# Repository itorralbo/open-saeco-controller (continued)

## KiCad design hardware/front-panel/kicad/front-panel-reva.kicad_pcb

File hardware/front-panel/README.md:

# Frontal Rev A.0

Decisión del propietario, 2026-09-16: reproducir la PCB frontal para conservar
la disposición de botones y montar una pantalla nueva compatible con el hueco.
Se conserva como objetivo la geometría original. El 2026-09-18 se recuperaron por
fotogrametría contorno, taladros y centros de los siete pulsadores (184 × 54,3 mm);
están aceptadas como línea base del layout y aplicadas a la PCB de trabajo. Ver
[registro mecánico](mechanical.md).

Estado del layout (2026-09-18): **PCB colocada y ruteada, DRC limpio y paquete JLCPCB
candidato**, pendiente de revisión antes de pedir. Ver [layout](layout.md).

## Entregables de esta iteración

- [Esquema KiCad](kicad/front-panel-reva.kicad_sch), con símbolos embebidos.
- [Proyecto KiCad](kicad/front-panel-reva.kicad_pro) y
  [PCB](kicad/front-panel-reva.kicad_pcb) colocada y ruteada, con huella propia de
  los pulsadores en [OpenSaeco.pretty](kicad/OpenSaeco.pretty/).
- [Layout, mapa de teclas y registros del TCA9534](layout.md);
  vistas [superior](preview/pcb-top.png) e [inferior](preview/pcb-bottom.png).
- [Paquete JLCPCB candidato](fabrication/): Gerber y taladros, BOM y CPL.
- [Vista nativa de KiCad](validation/front-panel-reva.svg) y
  [validación y límites](../kicad-workflow.md).
- [Vista SVG del circuito](preview/front-panel.svg), generada como ayuda de revisión.
- [BOM candidata](bom-draft.csv) y [conexiones previstas](design-nets.json).
- [Contrato con la principal](../controller/front-panel-interface.md).
- [Registro mecánico fotogramétrico](mechanical.md), [datos](mechanical-source.json)
  y [plano 1:1 imprimible](validation/mechanical-1to1.svg).
- [Selección de componentes y montaje JLCPCB](../assembly/README.md): 42 de 42
  posiciones con MPN y código JLC; J1 (Würth WR-MM) sin stock en JLCPCB el
  2026-10-08, se compra aparte y se suelda a mano.

El circuito contiene alimentación externa de 3,3 V, un TCA9534PWR, siete canales
de pulsador filtrados (los siete de la PCB original), el LED de standby en el octavo
puerto y una salida a adaptador de display SPI. ERC y DRC nativos limpios. No está
pedido: faltan las comprobaciones de [layout.md](layout.md#pendiente-antes-de-pedir).

## Circuito propuesto

El ESP32 permanece en la controladora principal. Lee botones por I²C y escribe
la pantalla por SPI. El STM32 recibe solicitudes a través del protocolo del
proyecto y conserva la autoridad sobre las cargas.

U1 es un **TCA9534PWR, TSSOP-16**. A0/A1/A2 van a masa, dirección de siete bits
`0x20`. Sus ocho puertos arrancan como entradas; P0–P6 leen teclas y P7 se configura
como salida para el LED (ver [layout.md](layout.md#teclas-led-y-registros-del-tca9534)).
INT es una salida activa a nivel
bajo de drenador abierto. Ver pinout y registros en la
[hoja de datos TI SCPS197D](https://www.ti.com/lit/ds/symlink/tca9534.pdf),
§5, §8.5 y §8.6. El esquema y la BOM se refieren al TCA9534, no al TCA9534A.

Cada canal de tecla tiene 10 kΩ a 3,3 V, 100 nF a masa y un pulsador normalmente abierto
a masa a través de 1 kΩ. La resistencia serie limita la corriente si un error
configura el puerto como salida alta. Estimación nominal: 0,30 V pulsado,
0,30 mA por pulsador y constante de subida de 1 ms. El RC reduce ruido;
el antirrebote temporal sigue siendo necesario.

R1/R2 = 4,7 kΩ son las únicas pull-ups I²C previstas. R3 = 10 kΩ polariza INT.
C1 = 100 nF y C2 = 1 µF quedan junto a U1; C3 = 10 µF, junto al pin 1 de J1.
Las huellas 0603 tienen referencias de compra candidatas en la BOM; falta comprobar
capacitancia efectiva, temperatura, corriente y espacio. Se usan X7R para 100 nF
y X5R para 1 µF/10 µF según el catálogo de montaje consultado. Pulsadores: HRO
K2-1102SP-A4SC-04 (JLC C83916), 6 × 6 × 4,3 mm como el original medido.
LED STBY: KT-0603R rojo (C2286) con R7 = 470 Ω a 3,3 V, activo con P7 a 0.

J2 lleva alimentación, masa, MOSI, reloj, CS, DC, RESET y BL. CS y RESET
tienen pull-up; BL tiene pull-down para solicitar retroiluminación apagada al
arranque. **BL es una señal lógica**, prevista para un módulo con driver de LED.
No alimentar directamente una retroiluminación desde ese GPIO. J2 es un JST PH de
8 vías vertical (B8B-PH-K-S, JLC C157974) con el orden del cable PH del módulo
Waveshare 2" (VCC GND DIN CLK CS DC RST BL), útil para el banco. El adaptador
definitivo deberá respetar ese orden y añadir driver si lo necesita la pantalla.

J1 es el Würth WR-MM 690367181672 que el propietario identificó el 2026-10-01 en
el JP3 original, igual que J104 de la principal: 16 contactos a 1,27 mm al
tresbolillo. El cable original es plano, de 16 hilos y 1:1; su pestillo entra en
un taladro de 1,5 mm junto al pin 1, que lo retiene y fija el sentido. Va sobre la
zona del JP3 original, en su pestaña, cara de componentes. JLCPCB lo lista como C19103863 sin stock (2026-10-01).

## Pantalla reemplazable

> Decisión registrada (2026-09-18): se adopta un **TFT ST7789 2,0"** (240×320, SPI 4 hilos, 3,3 V) sobre frontal nuevo; se descarta reutilizar la PCB OEM. Ver [ADR-0001](../../docs/adr/0001-front-panel-display-st7789.md) y el [subsistema display + UI](../../docs/display-ui.md) (stack LVGL 9 + esp_lcd, SPI 10 MHz, presupuestos y árbol de pantallas). La tabla siguiente se conserva como registro de evaluación de hueco.

La compatibilidad se define por ventana visible, contorno total, altura,
orientación, lógica de 3,3 V, consumo y protocolo. La diagonal sola no basta.
La PCB de botones y el adaptador del display serán diseños independientes,
para cambiar de pantalla sin recolocar los pulsadores.

Referencias para comparar dimensiones, **sin selección ni compra todavía**:

| Módulo candidato | Controlador / resolución | Área visible (mm) | PCB del módulo (mm) |
|---|---|---|---|
| Waveshare 2 inch LCD Module | ST7789VW / 240 × 320 | 30,60 × 40,80 | 58,0 × 35,0 |
| Waveshare 2.4 inch LCD Module | ILI9341 / 240 × 320 | 36,72 × 48,96 | 70,50 × 43,30 |

Fuentes del fabricante consultadas el 2026-09-16:
[módulo 2 pulgadas](https://www.waveshare.com/product/displays/lcd-oled/2inch-lcd-module.htm)
y [módulo 2,4 pulgadas](https://www.waveshare.com/product/2.4inch-lcd-module.htm).
Para el segundo, el fabricante vincula el nivel lógico a la alimentación:
se evaluará alimentado a 3,3 V, no a 5 V.

Estos módulos sirven para evaluar el hueco y prototipar. El diseño final puede
necesitar un panel sin carrier comercial. J2 no incorpora MISO ni táctil:
un display que necesite lectura, touch o interfaz RGB/paralela requiere revisar
el adaptador y las señales disponibles, no solo cambiar el controlador software.

## Comportamiento de firmware previsto

1. Mantener BL bajo y CS alto durante la inicialización. Aplicar el reset y los
   tiempos del display finalmente seleccionado antes de habilitar la imagen.
2. Configurar U1 en este orden: Output (`0x01`) = `0xFF` (LED apagado), Polarity
   (`0x02`) = `0x00`, Configuration (`0x03`) = `0x7F`; leer Input (`0x00`) con los
   bits 0–6. P7 (bit 7 de Output) solo controla el LED, activo a 0.
3. Leer cada 5 ms como punto de partida y exigir 20 ms de estabilidad.
   INT permite adelantar una lectura; conservar el sondeo para detectar fallos.
   Son objetivos iniciales de firmware, aún no implementados ni ensayados.
4. Tras arranque/reconexión, esperar liberación de todos los botones antes de
   aceptar una pulsación. No convertir una tecla mantenida en START al reiniciar.
5. NACK, lectura caducada o fallo del bus invalidan el teclado: no equivalen a
   «ningún botón pulsado». El frontal no podrá generar nuevas solicitudes START.
   La política del ciclo en curso corresponde al STM32 y queda por definir.

U1 no dispone de reset externo: recuperar I²C y reescribir configuración puede
no bastar tras ciertos fallos de alimentación. La principal incorpora un corte
TPS2553 con límite de corriente para `3V3_UI`; quedan por ensayar la secuencia de apagado y la prevención
de alimentación parásita por GPIO con el display y el arnés definitivos.

## Comprobación y edición

`python3 tools/generate_front_panel.py` regenera esquema, SVG, BOM y conexiones.
El generador es la fuente inicial: no ejecutarlo sobre ediciones manuales de KiCad
sin incorporarlas primero. La vista SVG es una representación auxiliar, no una
exportación de KiCad ni evidencia de que su parser acepte el archivo.

`python3 tools/check_front_panel.py` comprueba las conexiones del archivo de
esquema contra requisitos del circuito. `python3 tools/validate_kicad.py` ejecuta
ERC y coteja la netlist nativa de KiCad contra los 42 componentes y 118 pines.
`python3 tools/render_front_panel_mechanics.py` regenera el plano 1:1 y
`python3 tools/apply_front_panel_mechanics.py` aplica contorno, taladros y
referencias a la PCB desde [mechanical-source.json](mechanical-source.json).
`tools/sync_front_panel_pcb.py` y `tools/layout_front_panel_pcb.py` (Python de KiCad)
llevan las huellas a la PCB, colocan y rutean con Freerouting; `python3
tools/export_front_panel_fab.py` genera el paquete JLCPCB. Detalle en [layout.md](layout.md).

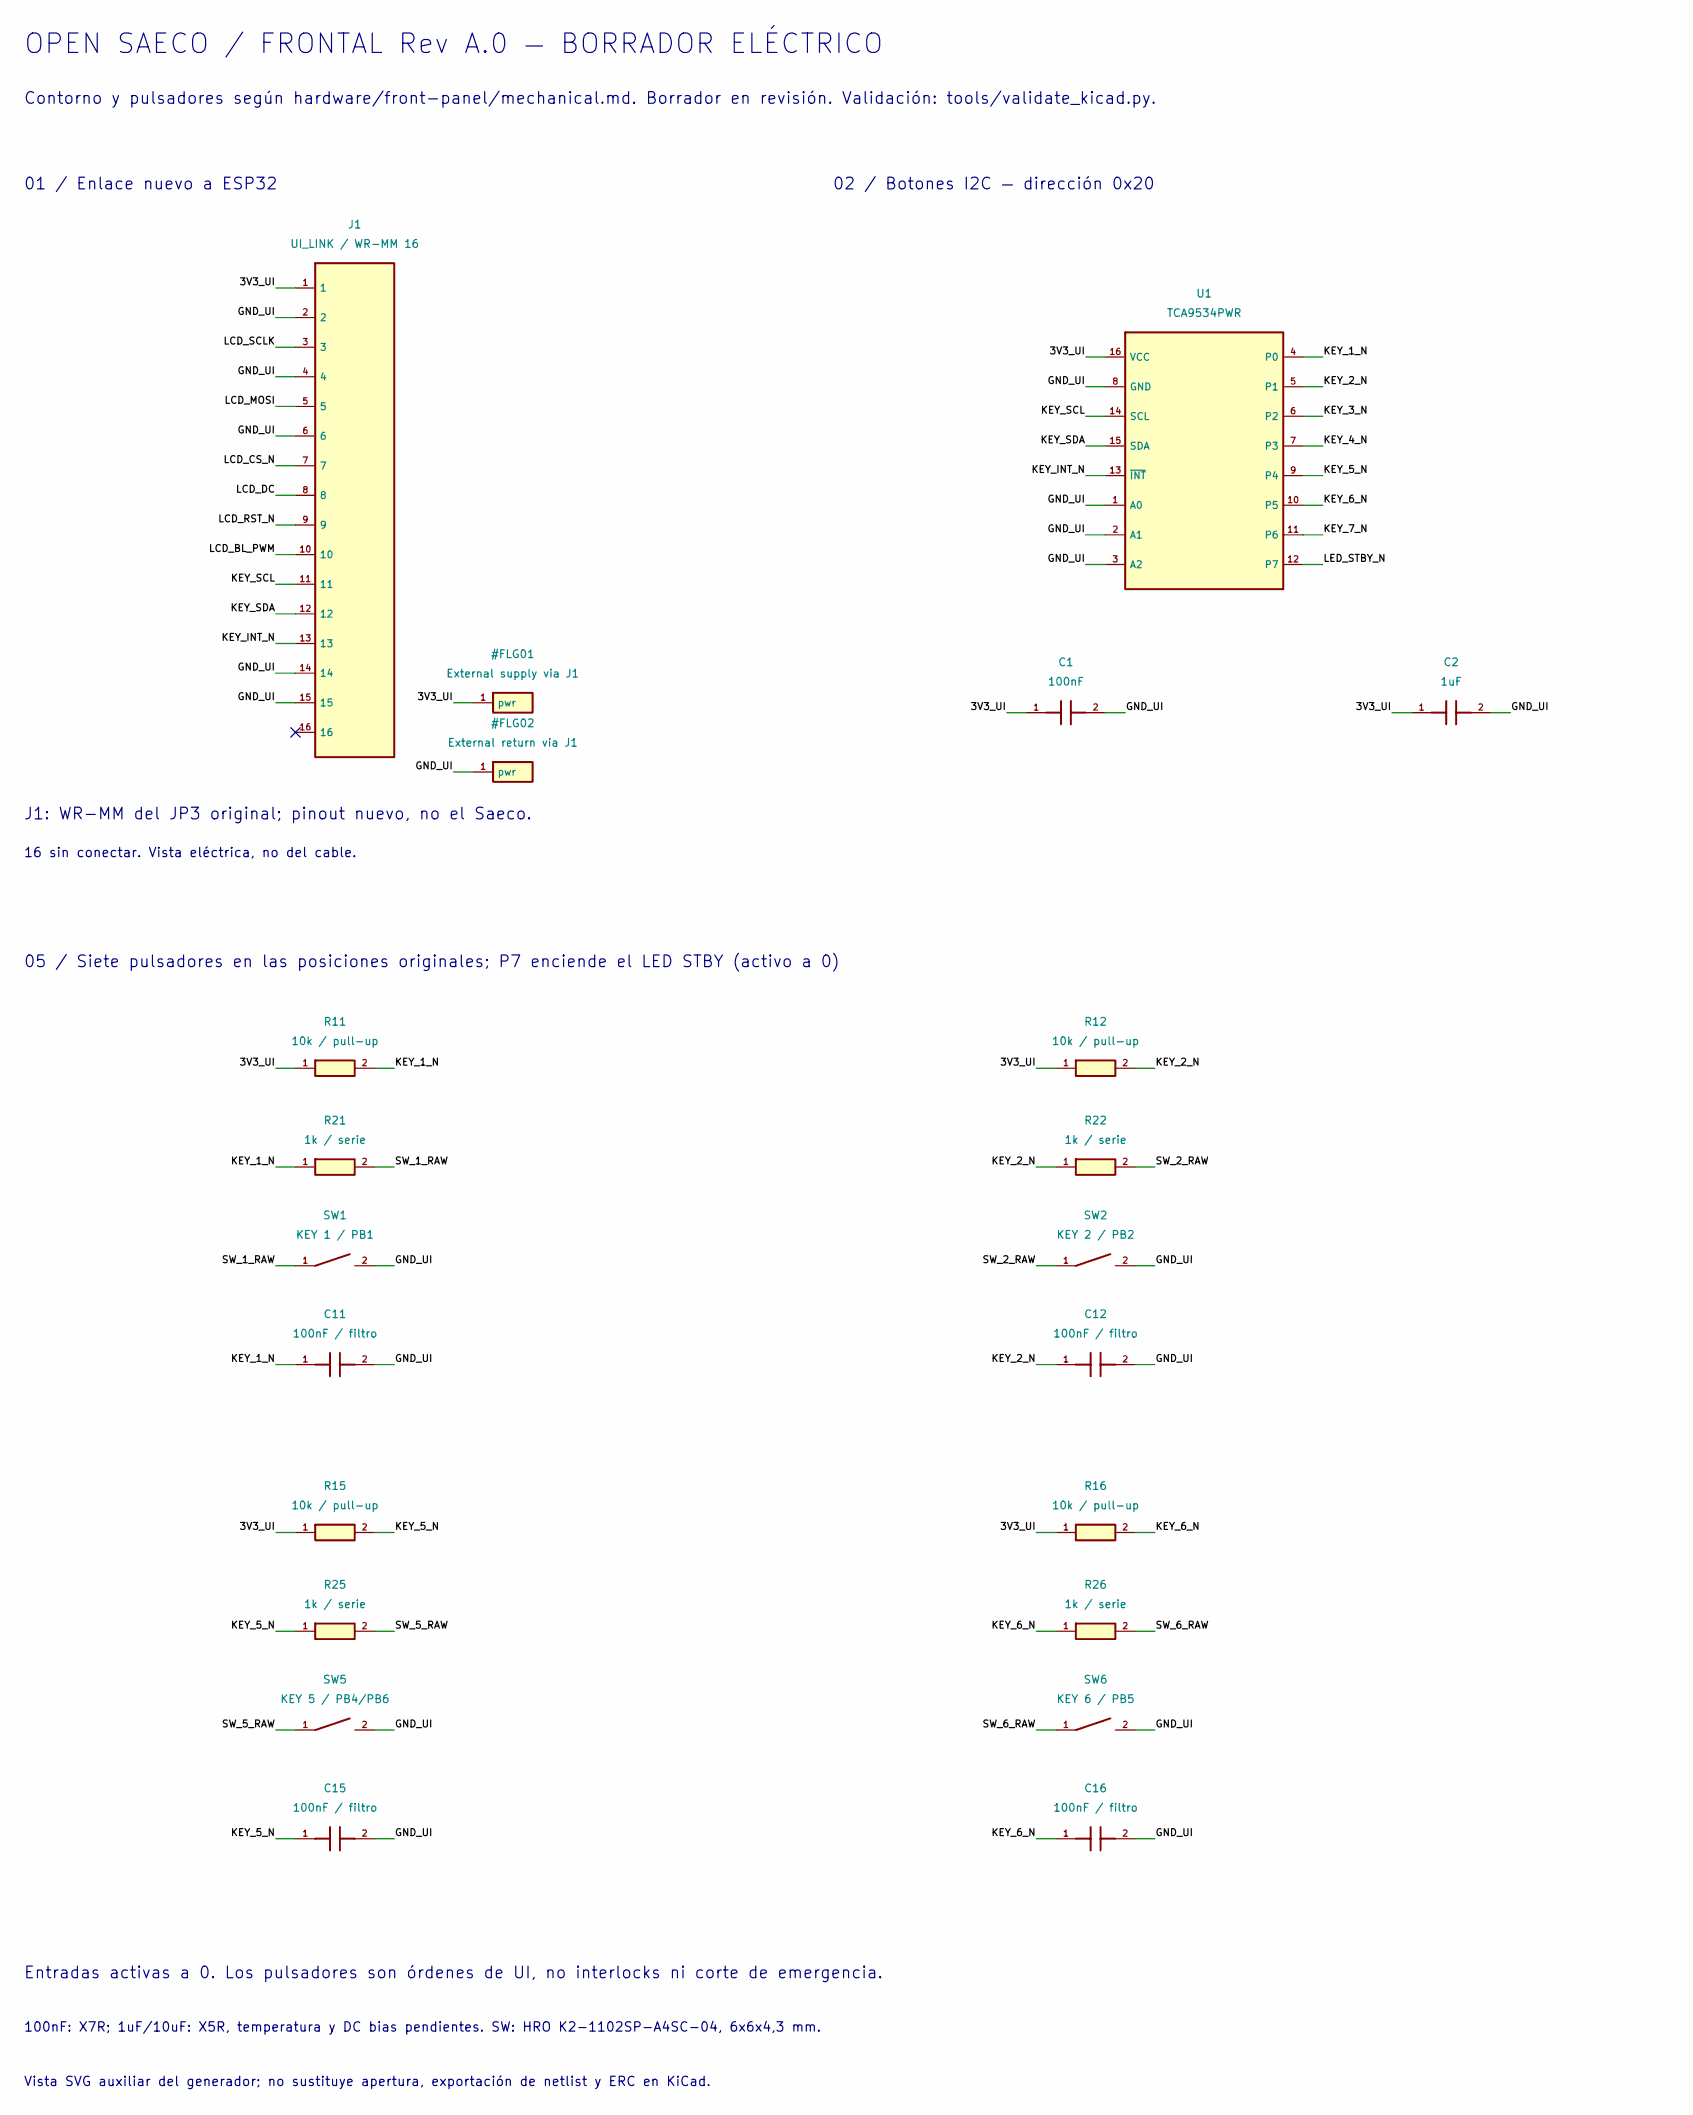
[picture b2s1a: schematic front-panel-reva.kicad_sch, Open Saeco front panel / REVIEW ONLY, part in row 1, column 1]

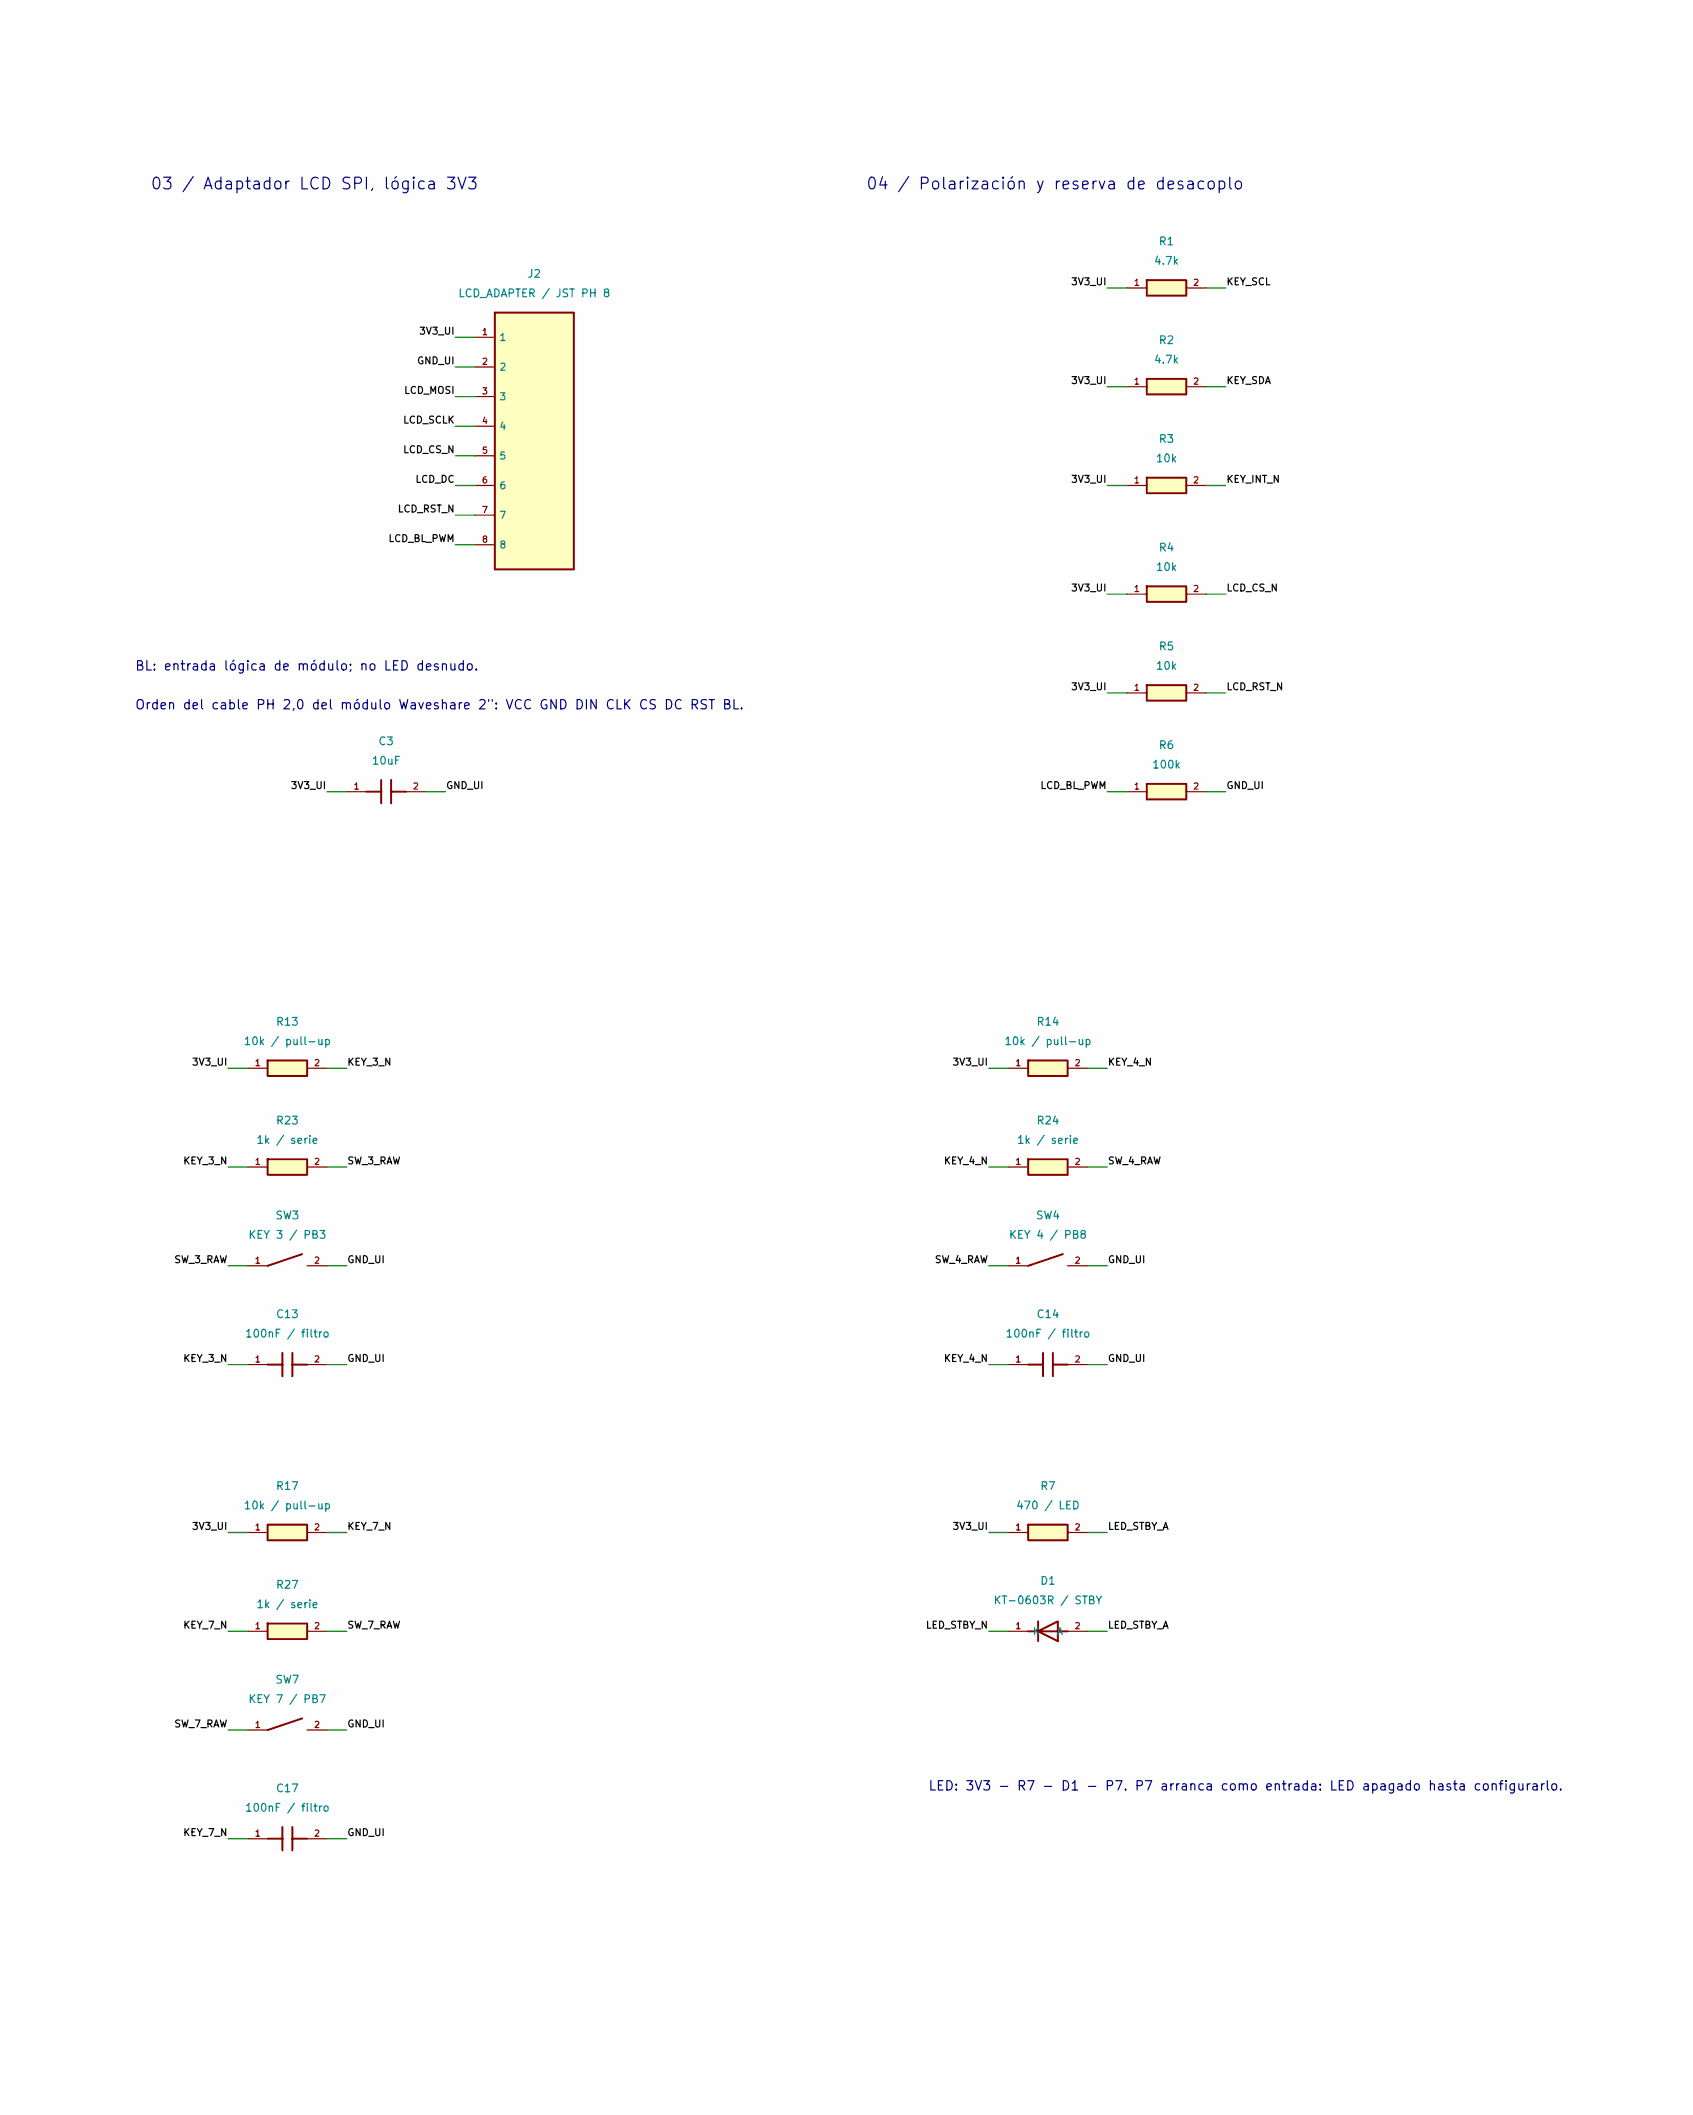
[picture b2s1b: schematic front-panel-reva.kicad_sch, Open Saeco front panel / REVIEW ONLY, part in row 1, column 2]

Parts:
C1: 100nF; C_0603_1608Metric; mpn CC0603KRX7R9BB104; lcsc C14663
C2: 1uF; C_0603_1608Metric; mpn CL10A105KB8NNNC; lcsc C15849
C3: 10uF; C_0603_1608Metric; mpn CL10A106MA8NRNC; lcsc C96446
C11, C12, C13, C14, C15, C16, C17: 100nF / filtro; C_0603_1608Metric; mpn CC0603KRX7R9BB104; lcsc C14663
D1: KT-0603R / STBY; LED_0603_1608Metric; mpn KT-0603R; lcsc C2286
J1: UI_LINK / WR-MM 16; Wurth_WR-MM_690367181672_2x08_P1.27mm_Vertical; mpn 690367181672; lcsc C19103863
J2: LCD_ADAPTER / JST PH 8; JST_PH_B8B-PH-K_1x08_P2.00mm_Vertical; mpn B8B-PH-K-S(LF)(SN); lcsc C157974
R1, R2: 4.7k; R_0603_1608Metric; mpn 0603WAF4701T5E; lcsc C23162
R3, R4, R5: 10k; R_0603_1608Metric; mpn 0603WAF1002T5E; lcsc C25804
R6: 100k; R_0603_1608Metric; mpn 0603WAF1003T5E; lcsc C25803
R7: 470 / LED; R_0603_1608Metric; mpn 0603WAF4700T5E; lcsc C23179
R11, R12, R13, R14, R15, R16, R17: 10k / pull-up; R_0603_1608Metric; mpn 0603WAF1002T5E; lcsc C25804
R21, R22, R23, R24, R25, R26, R27: 1k / serie; R_0603_1608Metric; mpn 0603WAF1001T5E; lcsc C21190
SW1: KEY 1 / PB1; SW_HRO_K2-1102SP-A4SC-04; mpn K2-1102SP-A4SC-04; lcsc C83916
SW2: KEY 2 / PB2; SW_HRO_K2-1102SP-A4SC-04; mpn K2-1102SP-A4SC-04; lcsc C83916
SW3: KEY 3 / PB3; SW_HRO_K2-1102SP-A4SC-04; mpn K2-1102SP-A4SC-04; lcsc C83916
SW4: KEY 4 / PB8; SW_HRO_K2-1102SP-A4SC-04; mpn K2-1102SP-A4SC-04; lcsc C83916
SW5: KEY 5 / PB4/PB6; SW_HRO_K2-1102SP-A4SC-04; mpn K2-1102SP-A4SC-04; lcsc C83916
SW6: KEY 6 / PB5; SW_HRO_K2-1102SP-A4SC-04; mpn K2-1102SP-A4SC-04; lcsc C83916
SW7: KEY 7 / PB7; SW_HRO_K2-1102SP-A4SC-04; mpn K2-1102SP-A4SC-04; lcsc C83916
U1: TCA9534PWR; TSSOP-16_4.4x5mm_P0.65mm; mpn TCA9534PWR; lcsc C783615

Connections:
/3V3_UI: C1.1, C2.1, C3.1, J1.1, J2.1, R1.1, R2.1, R3.1, R4.1, R5.1, R7.1, R11.1, R12.1, R13.1, R14.1, R15.1, R16.1, R17.1, U1.16 (VCC)
/GND_UI: C1.2, C2.2, C3.2, C11.2, C12.2, C13.2, C14.2, C15.2, C16.2, C17.2, J1.2, J1.4, J1.6, J1.14, J1.15, J2.2, R6.2, SW1.2, SW2.2, SW3.2, SW4.2, SW5.2, SW6.2, SW7.2, U1.1 (A0), U1.2 (A1), U1.3 (A2), U1.8 (GND)
/KEY_1_N: C11.1, R11.2, R21.1, U1.4 (P0)
/KEY_2_N: C12.1, R12.2, R22.1, U1.5 (P1)
/KEY_3_N: C13.1, R13.2, R23.1, U1.6 (P2)
/KEY_4_N: C14.1, R14.2, R24.1, U1.7 (P3)
/KEY_5_N: C15.1, R15.2, R25.1, U1.9 (P4)
/KEY_6_N: C16.1, R16.2, R26.1, U1.10 (P5)
/KEY_7_N: C17.1, R17.2, R27.1, U1.11 (P6)
/KEY_INT_N: J1.13, R3.2, U1.13 (~INT)
/KEY_SCL: J1.11, R1.2, U1.14 (SCL)
/KEY_SDA: J1.12, R2.2, U1.15 (SDA)
/LCD_BL_PWM: J1.10, J2.8, R6.1
/LCD_CS_N: J1.7, J2.5, R4.2
/LCD_DC: J1.8, J2.6
/LCD_MOSI: J1.5, J2.3
/LCD_RST_N: J1.9, J2.7, R5.2
/LCD_SCLK: J1.3, J2.4
/LED_STBY_A: D1.2 (A), R7.2
/LED_STBY_N: D1.1 (K), U1.12 (P7)
/SW_1_RAW: R21.2, SW1.1
/SW_2_RAW: R22.2, SW2.1
/SW_3_RAW: R23.2, SW3.1
/SW_4_RAW: R24.2, SW4.1
/SW_5_RAW: R25.2, SW5.1
/SW_6_RAW: R26.2, SW6.1
/SW_7_RAW: R27.2, SW7.1

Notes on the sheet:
OPEN SAECO / FRONTAL Rev A.0 — BORRADOR ELÉCTRICO
Contorno y pulsadores según hardware/front-panel/mechanical.md. Borrador en revisión. Validación: tools/validate_kicad.py.
01 / Enlace nuevo a ESP32
J1: WR-MM del JP3 original; pinout nuevo, no el Saeco.
16 sin conectar. Vista eléctrica, no del cable.
02 / Botones I2C — dirección 0x20
03 / Adaptador LCD SPI, lógica 3V3
Orden del cable PH 2,0 del módulo Waveshare 2": VCC GND DIN CLK CS DC RST BL.
BL: entrada lógica de módulo; no LED desnudo.
04 / Polarización y reserva de desacoplo
05 / Siete pulsadores en las posiciones originales; P7 enciende el LED STBY (activo a 0)
LED: 3V3 - R7 - D1 - P7. P7 arranca como entrada: LED apagado hasta configurarlo.
Entradas activas a 0. Los pulsadores son órdenes de UI, no interlocks ni corte de emergencia.
100nF: X7R; 1uF/10uF: X5R, temperatura y DC bias pendientes. SW: HRO K2-1102SP-A4SC-04, 6x6x4,3 mm.
Vista SVG auxiliar del generador; no sustituye apertura, exportación de netlist y ERC en KiCad.

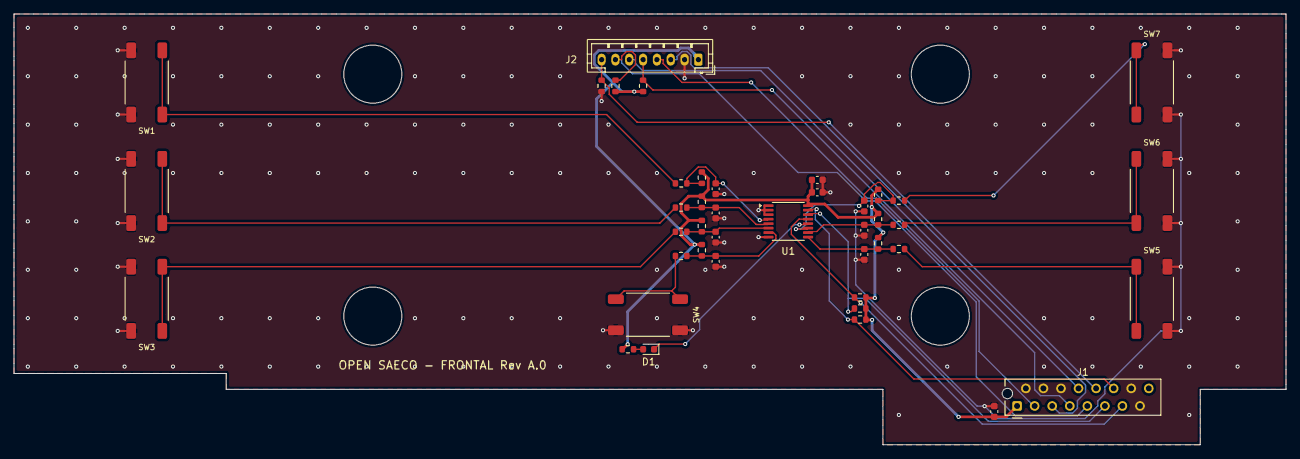
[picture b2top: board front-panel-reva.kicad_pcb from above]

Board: 2 copper layers, 184.0 x 62.3 mm, 42 parts (0 on the bottom side), 27 nets.

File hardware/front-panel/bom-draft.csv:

reference,value,footprint,status,manufacturer,mpn,lcsc,jlc_class,pcba_type
J1,UI_LINK / WR-MM 16,OpenSaeco:Wurth_WR-MM_690367181672_2x08_P1.27mm_Vertical,owner_identified_supply_pending,Wurth Elektronik,690367181672,C19103863,Extended,TBD
U1,TCA9534PWR,Package_SO:TSSOP-16_4.4x5mm_P0.65mm,candidate,Texas Instruments,TCA9534PWR,C783615,Extended,Economic and Standard
C1,100nF,Capacitor_SMD:C_0603_1608Metric,candidate,YAGEO,CC0603KRX7R9BB104,C14663,Basic,Economic and Standard
C2,1uF,Capacitor_SMD:C_0603_1608Metric,candidate,Samsung Electro-Mechanics,CL10A105KB8NNNC,C15849,Basic,Economic and Standard
J2,LCD_ADAPTER / JST PH 8,Connector_JST:JST_PH_B8B-PH-K_1x08_P2.00mm_Vertical,candidate,JST,B8B-PH-K-S(LF)(SN),C157974,Extended,TBD
R1,4.7k,Resistor_SMD:R_0603_1608Metric,candidate,UNI-ROYAL,0603WAF4701T5E,C23162,Basic,Economic and Standard
R2,4.7k,Resistor_SMD:R_0603_1608Metric,candidate,UNI-ROYAL,0603WAF4701T5E,C23162,Basic,Economic and Standard
R3,10k,Resistor_SMD:R_0603_1608Metric,candidate,UNI-ROYAL,0603WAF1002T5E,C25804,Basic,Economic and Standard
R4,10k,Resistor_SMD:R_0603_1608Metric,candidate,UNI-ROYAL,0603WAF1002T5E,C25804,Basic,Economic and Standard
R5,10k,Resistor_SMD:R_0603_1608Metric,candidate,UNI-ROYAL,0603WAF1002T5E,C25804,Basic,Economic and Standard
R6,100k,Resistor_SMD:R_0603_1608Metric,candidate,UNI-ROYAL,0603WAF1003T5E,C25803,Basic,Economic and Standard
C3,10uF,Capacitor_SMD:C_0603_1608Metric,candidate,Samsung Electro-Mechanics,CL10A106MA8NRNC,C96446,Basic,Economic and Standard
R11,10k / pull-up,Resistor_SMD:R_0603_1608Metric,candidate,UNI-ROYAL,0603WAF1002T5E,C25804,Basic,Economic and Standard
R21,1k / serie,Resistor_SMD:R_0603_1608Metric,candidate,UNI-ROYAL,0603WAF1001T5E,C21190,Basic,Economic and Standard
SW1,KEY 1 / PB1,OpenSaeco:SW_HRO_K2-1102SP-A4SC-04,candidate,Korean Hroparts Elec,K2-1102SP-A4SC-04,C83916,Extended,Economic and Standard
C11,100nF / filtro,Capacitor_SMD:C_0603_1608Metric,candidate,YAGEO,CC0603KRX7R9BB104,C14663,Basic,Economic and Standard
R12,10k / pull-up,Resistor_SMD:R_0603_1608Metric,candidate,UNI-ROYAL,0603WAF1002T5E,C25804,Basic,Economic and Standard
R22,1k / serie,Resistor_SMD:R_0603_1608Metric,candidate,UNI-ROYAL,0603WAF1001T5E,C21190,Basic,Economic and Standard
SW2,KEY 2 / PB2,OpenSaeco:SW_HRO_K2-1102SP-A4SC-04,candidate,Korean Hroparts Elec,K2-1102SP-A4SC-04,C83916,Extended,Economic and Standard
C12,100nF / filtro,Capacitor_SMD:C_0603_1608Metric,candidate,YAGEO,CC0603KRX7R9BB104,C14663,Basic,Economic and Standard
R13,10k / pull-up,Resistor_SMD:R_0603_1608Metric,candidate,UNI-ROYAL,0603WAF1002T5E,C25804,Basic,Economic and Standard
R23,1k / serie,Resistor_SMD:R_0603_1608Metric,candidate,UNI-ROYAL,0603WAF1001T5E,C21190,Basic,Economic and Standard
SW3,KEY 3 / PB3,OpenSaeco:SW_HRO_K2-1102SP-A4SC-04,candidate,Korean Hroparts Elec,K2-1102SP-A4SC-04,C83916,Extended,Economic and Standard
C13,100nF / filtro,Capacitor_SMD:C_0603_1608Metric,candidate,YAGEO,CC0603KRX7R9BB104,C14663,Basic,Economic and Standard
R14,10k / pull-up,Resistor_SMD:R_0603_1608Metric,candidate,UNI-ROYAL,0603WAF1002T5E,C25804,Basic,Economic and Standard
R24,1k / serie,Resistor_SMD:R_0603_1608Metric,candidate,UNI-ROYAL,0603WAF1001T5E,C21190,Basic,Economic and Standard
SW4,KEY 4 / PB8,OpenSaeco:SW_HRO_K2-1102SP-A4SC-04,candidate,Korean Hroparts Elec,K2-1102SP-A4SC-04,C83916,Extended,Economic and Standard
C14,100nF / filtro,Capacitor_SMD:C_0603_1608Metric,candidate,YAGEO,CC0603KRX7R9BB104,C14663,Basic,Economic and Standard
R15,10k / pull-up,Resistor_SMD:R_0603_1608Metric,candidate,UNI-ROYAL,0603WAF1002T5E,C25804,Basic,Economic and Standard
R25,1k / serie,Resistor_SMD:R_0603_1608Metric,candidate,UNI-ROYAL,0603WAF1001T5E,C21190,Basic,Economic and Standard
SW5,KEY 5 / PB4/PB6,OpenSaeco:SW_HRO_K2-1102SP-A4SC-04,candidate,Korean Hroparts Elec,K2-1102SP-A4SC-04,C83916,Extended,Economic and Standard
C15,100nF / filtro,Capacitor_SMD:C_0603_1608Metric,candidate,YAGEO,CC0603KRX7R9BB104,C14663,Basic,Economic and Standard
R16,10k / pull-up,Resistor_SMD:R_0603_1608Metric,candidate,UNI-ROYAL,0603WAF1002T5E,C25804,Basic,Economic and Standard
R26,1k / serie,Resistor_SMD:R_0603_1608Metric,candidate,UNI-ROYAL,0603WAF1001T5E,C21190,Basic,Economic and Standard
SW6,KEY 6 / PB5,OpenSaeco:SW_HRO_K2-1102SP-A4SC-04,candidate,Korean Hroparts Elec,K2-1102SP-A4SC-04,C83916,Extended,Economic and Standard
C16,100nF / filtro,Capacitor_SMD:C_0603_1608Metric,candidate,YAGEO,CC0603KRX7R9BB104,C14663,Basic,Economic and Standard
R17,10k / pull-up,Resistor_SMD:R_0603_1608Metric,candidate,UNI-ROYAL,0603WAF1002T5E,C25804,Basic,Economic and Standard
R27,1k / serie,Resistor_SMD:R_0603_1608Metric,candidate,UNI-ROYAL,0603WAF1001T5E,C21190,Basic,Economic and Standard
SW7,KEY 7 / PB7,OpenSaeco:SW_HRO_K2-1102SP-A4SC-04,candidate,Korean Hroparts Elec,K2-1102SP-A4SC-04,C83916,Extended,Economic and Standard
C17,100nF / filtro,Capacitor_SMD:C_0603_1608Metric,candidate,YAGEO,CC0603KRX7R9BB104,C14663,Basic,Economic and Standard
R7,470 / LED,Resistor_SMD:R_0603_1608Metric,candidate,UNI-ROYAL,0603WAF4700T5E,C23179,Basic,Economic and Standard
D1,KT-0603R / STBY,LED_SMD:LED_0603_1608Metric,candidate,Hubei KENTO Elec,KT-0603R,C2286,Basic,Economic and Standard

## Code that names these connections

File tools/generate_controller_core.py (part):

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        d.DEFS[f'J{n}'] = (d.connector(n), 5.08, n*1.905+1.27)
    v, g = '3V3_CORE', 'GND_UI'
    stm = {'VBAT': v, 'VDD': v, 'VSS': g, 'VSSA': g, 'VDDA': v, 'VREF+': v,
           'NRST': 'STM_NRST', 'PB8': 'STM_BOOT0', 'PA13': 'STM_SWDIO',
           'PA14': 'STM_SWCLK', 'PB3': 'STM_SWO',
           'PA9': 'STM_TX_RAW', 'PA10': 'ESP_TO_STM', 'PB12': 'UI_PWR_EN',
           'PA3': 'NTC_ADC', 'PA2': 'FLOW_TIM', 'PA1': 'DOOR_CLOSED_N',
           'PC3': 'WATER_LEVEL', 'PC2': 'BU_PRESENT_N', 'PA0': 'BU_WORK_N',
           'PC0': 'BREW_CURRENT_ADC', 'PF1': 'RAIL_12V_ADC',
           'PC1': 'RAIL_24V_ADC', 'PC14': 'BREW_DIR_RAW',
           'PA7': 'VALVE_EN_RAW',
           'PF0': 'BREW_PWM_RAW', 'PB5': 'BREW_SLEEP_RAW',
           'PB4': 'WATCHDOG_KICK_RAW', 'PB6': 'BREW_FAULT_N',
           'PB7': 'MAINS_ARM_RAW', 'PC5': 'HEATER_EN_RAW',
           'PB11': 'PUMP_EN_RAW', 'PC4': 'GRINDER_EN_RAW',
           'PA6': 'GRINDER_CURRENT_ADC', 'PB14': 'HS_NTC_ADC'}
    esp = {'GND': g, 'EP_GND': g, '3V3': v, 'EN': 'ESP_EN', 'IO0': 'ESP_BOOT0',
           'IO42': 'ESP_TX_RAW', 'IO2': 'STM_TO_ESP', 'TXD0': 'ESP_DEBUG_TX',
           'RXD0': 'ESP_DEBUG_RX', 'IO4': 'KEY_SDA', 'IO5': 'KEY_SCL',
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    d.passive('R305','R','1k / UI discharge',840,218,'3V3_UI',g)
    d.passive('C308','C','1uF / switch input',625,196,v,g)
    d.passive('C309','C','10uF / switch output',795,196,'3V3_UI',g)
    d.note('PB12 controla UI_PWR_EN; pull-up mantiene el frontal encendido durante reset.',610,244,1.2)
    d.note('ILIM 475-565 mA y apagado térmico; R305 descarga el frontal al apagarlo. FAULT sin conectar.',610,250,1.2)

    d.note('09 / USB-C de servicio — datos ESP32 y alimentación de banco opcional',610,276,1.8)
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
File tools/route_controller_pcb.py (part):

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    # (V1 red, V2 blue), the strapped blacks V3/V4, the presence greens V5/V6
    # and the work reds V7/V8. Pads 5 and 6 are strapped: the brew-unit
    # contact common.
    track(board, '/BU_BRIDGE', (3.5, 52.0), (3.5, 54.5), width=PIN_WIDTH)

    # Brew-unit present and working contacts (J108 pads 4 and 2), each with
    # its other pad on the ground fill, east on F.Cu to their dividers.
    polyline(board, '/BU_PRESENT_RAW', [(3.5, 57.0), (10.5, 57.0), (12.825, 54.675),
                                        (12.825, 51.175), (19.0, 51.175)],
             width=PIN_WIDTH)
    track(board, '/BU_PRESENT_N', (19.0, 52.825), (22.0, 52.775), width=PIN_WIDTH)
    polyline(board, '/BU_WORK_RAW', [(3.5, 62.0), (12.5, 62.0), (14.175, 60.325),
                                     (14.175, 58.175), (19.0, 58.175)], width=PIN_WIDTH)
    track(board, '/BU_WORK_N', (19.0, 59.825), (22.0, 59.775), width=PIN_WIDTH)

    # Door contact (JP14).
    polyline(board, '/DOOR_RAW', [(3.0, 73.5), (6.0, 73.5), (7.675, 71.825),
                                  (15.0, 71.825)], width=PIN_WIDTH)
    polyline(board, '/DOOR_RAW', [(15.475, 71.825), (15.675, 71.825), (16.5, 71.0), (16.775, 71.0),
                                  (17.6, 70.175)], width=PIN_WIDTH)
    track(board, '/DOOR_CLOSED_N', (18.0, 71.825), (21.0, 71.775), width=PIN_WIDTH)

    # NTC (JP13): raw net up the gap between the pull-up and the series part.
    polyline(board, '/NTC_RAW', [(28.75, 125.3), (29.5, 124.55), (29.5, 106.5), (29.8, 106.5),
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                                  (32.725, 109.2)], width=PIN_WIDTH)
    polyline(board, '/FLOW_RAW', [(33.6, 110.3), (33.6, 111.0), (32.725, 111.0)],
             width=PIN_WIDTH)
    track(board, '/FLOW_TIM', (31.075, 111.0), (31.075, 112.8), width=PIN_WIDTH)

    # Water level (JP22): R411 drops to B.Cu and runs straight down under the
    # valve return to the connector.
    track(board, '/WATER_RAW', (19.0, 117.0), (20.5, 118.5), width=PIN_WIDTH)
    via(board, '/WATER_RAW', (20.5, 118.5))
    # J109 is a JST ZH B3B-ZR (1.5 mm) since 2026-10-10: pin 2 sits right
    # under the drop.
    track(board, '/WATER_RAW', (20.5, 118.5), (20.5, 128.2), pcb.B_Cu, width=PIN_WIDTH)
    polyline(board, '/WATER_LEVEL', [(19.0, 115.175), (19.725, 115.9), (20.5, 115.9),
                                     (21.375, 116.775), (22.0, 116.775)], width=PIN_WIDTH)
    # DNP bias pair above J109 (issue #7): each end drops straight into its
    # header pin on F.Cu; R416's GND pad joins the fill.
    track(board, '/WATER_RAW', (20.425, 124.8), (22.075, 124.8), width=PIN_WIDTH)
    track(board, '/WATER_RAW', (20.5, 124.8), (20.5, 128.2), width=PIN_WIDTH)
    polyline(board, '/WATER_VCC', [(18.775, 124.8), (18.775, 126.3), (19.0, 126.525),
                                   (19.0, 128.2)], width=PIN_WIDTH)

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    polyline(board, ui, [(3.55, 15.863), (3.55, 9.15), (6.2, 6.5)], width=0.5)
    track(board, ui, (2.0, 12.775), (3.55, 12.775), width=0.5)
    track(board, ui, (2.0, 12.775), (1.95, 14.255), width=PIN_WIDTH)
    polyline(board, '/UI_ILIM', [(4.5, 15.863), (4.5, 15.0), (5.45, 14.125)], width=PIN_WIDTH)
    track(board, '/UI_PWR_EN', (5.45, 18.137), (6.975, 18.138), width=PIN_WIDTH)

    for start, point in (((4.5, 18.137), (4.5, 19.9)),
                         ((5.45, 12.475), (5.45, 11.2)),
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    fenced in by the ground stub of pin 4 and the reset loop of pin 2, so it
    drops to B.Cu inside the loop and runs
    south under the relay-return and 12 V branches to the LED driver's gate
    resistor. The MCU side of HEATER_EN_RAW (PC5) arrives on B.Cu through
    route_load_bus.
    """
    raw, gated = '/HEATER_EN_RAW', '/HEATER_EN_INTERLOCK'
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                                       (28.0, 94.2), (34.5, 94.2), (35.175, 94.875),
                                       (35.175, 95.5)], width=0.5)
    # Anode and return climb under the trunk on parallel B.Cu diagonals.
    track(board, '/HEATER_LED_ANODE', (36.825, 96.0), (40.0, 96.0), width=PIN_WIDTH)
    via(board, '/HEATER_LED_ANODE', (40.0, 96.0))
    polyline(board, '/HEATER_LED_ANODE', [(40.0, 96.0), (44.6, 91.4), (44.6, 88.9)],
             pcb.B_Cu, width=PIN_WIDTH)
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    track(board, '/HEATER_LED_RETURN', (45.35, 91.4), (OPTO_SELV_STUB_END, 90.54),
          width=PIN_WIDTH)
    opto_stubs(board, 'U701', {1: '/HEATER_LED_ANODE', 2: '/HEATER_LED_RETURN'})
    track(board, '/HEATER_LED_GATE', (31.825, 99.0), (31.825, 96.0), width=PIN_WIDTH)
    polyline(board, '/HEATER_LED_GATE', [(31.825, 99.0), (33.8, 99.0), (34.25, 98.55),
                                         (36.5, 98.55)], width=PIN_WIDTH)
    for start, point in (((30.175, 96.0), (28.9, 96.0)),
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    track(board, '/PUMP_LED_RETURN', (44.737, 116.0), (OPTO_SELV_STUB_END, 116.0),
          width=PIN_WIDTH)
    opto_stubs(board, 'U702', {1: '/PUMP_LED_ANODE', 2: '/PUMP_LED_RETURN'})
    track(board, '/PUMP_LED_GATE', (44.125, 106.6), (44.125, 108.2), width=PIN_WIDTH)
    polyline(board, '/PUMP_LED_GATE', [(44.125, 108.2), (43.5, 108.2), (43.5, 115.05),
                                       (42.862, 115.05)],
             width=PIN_WIDTH)
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    polyline(board, v12, [(54.35, 41.4), (54.675, 41.725), (54.675, 42.75)], width=0.3)
    polyline(board, '/PROBE_12V', [(56.325, 42.75), (56.325, 42.3), (55.62, 41.6),
                                    (55.62, 40.0)], width=PIN_WIDTH)
    track(board, '/PROBE_3V3', (50.54, 42.575), (50.54, 40.0), width=PIN_WIDTH)
    track(board, '/3V3_CORE', (50.54, 44.225), (49.4, 44.4), width=PIN_WIDTH)
    via(board, '/3V3_CORE', (49.4, 44.4))
    polyline(board, '/PROBE_24V', [(62.6, 42.675), (62.6, 41.9), (61.3, 40.6),
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    in the order of their filters, north to south, and every net uses two
    vias, one beside the MCU and one at its filter.

    - PC1 (pin 9.0) now carries RAIL_24V_ADC; PA5 is free. It is the only
      west-side pin north of the escape pocket that can reach J114.6.
    - PC3, PC2, PA0, PA1, PA2 and PA3 (pins 11, 10, 12, 13, 14 and 17) carry
      water, group present, group at work, door, flow (TIM2_CH3) and NTC
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
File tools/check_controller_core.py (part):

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        assert nets['U101'][str(pin)] == v, f'STM power pad {pin}'
    for pin in (15,27,31,47,63):
        assert nets['U101'][str(pin)] == g, f'STM ground pad {pin}'
    for pin, net in {7:'STM_NRST',43:'STM_TX_RAW',44:'ESP_TO_STM',49:'STM_SWDIO',
                     50:'STM_SWCLK',56:'STM_SWO',61:'STM_BOOT0',34:'UI_PWR_EN',
                     17:'NTC_ADC',14:'FLOW_TIM',13:'DOOR_CLOSED_N',10:'BU_PRESENT_N',
                     11:'WATER_LEVEL',12:'BU_WORK_N',8:'BREW_CURRENT_ADC',
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        assert nets['U201'][str(pin)] == g, f'ESP ground/EP pad {pin}'
    for pin in (28,29,30):
        assert nets['U201'][str(pin)] is None, 'Do not use octal PSRAM pins'
    for pin, net in {3:'ESP_EN',27:'ESP_BOOT0',35:'ESP_TX_RAW',38:'STM_TO_ESP',
                     4:'KEY_SDA',5:'KEY_SCL',6:'KEY_INT_N',7:'BL_RAW',12:'RST_RAW',
                     17:'DC_RAW',18:'CS_RAW',19:'MOSI_RAW',20:'SCLK_RAW',
                     13:'USB_DM_RAW',14:'USB_DP_RAW',8:'USB_VBUS_SENSE'}.items():
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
